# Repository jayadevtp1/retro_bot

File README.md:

# Desktop Bot

Desktop Bot is a mini AI companion robot built to sit right on my desk and bring a bit of personality to my workspace. Inspired by the M5Stack Chan AI bot and the nostalgic charm of vintage CRT monitors, I wanted to create a compact, expressive desk buddy that can react, chat
and emotions on a crisp 2-inch LCD screen.

# Features

• Animated Facial Expressions: Displays expressive eyes and emotions on a crisp 2-inch LCD screen.

• Built-in Voice Interaction: Listens and talks back naturally using an onboard digital mic and speaker amplifier.

• Desk Utilities: Doubles as a handy desk gadget with a digital clock and ambient temperature display.

• Capacitive Touch Interaction: Responds to gentle taps and head pats with playful expressions and reactions.
# Schematic & PCB

# Final Assembly

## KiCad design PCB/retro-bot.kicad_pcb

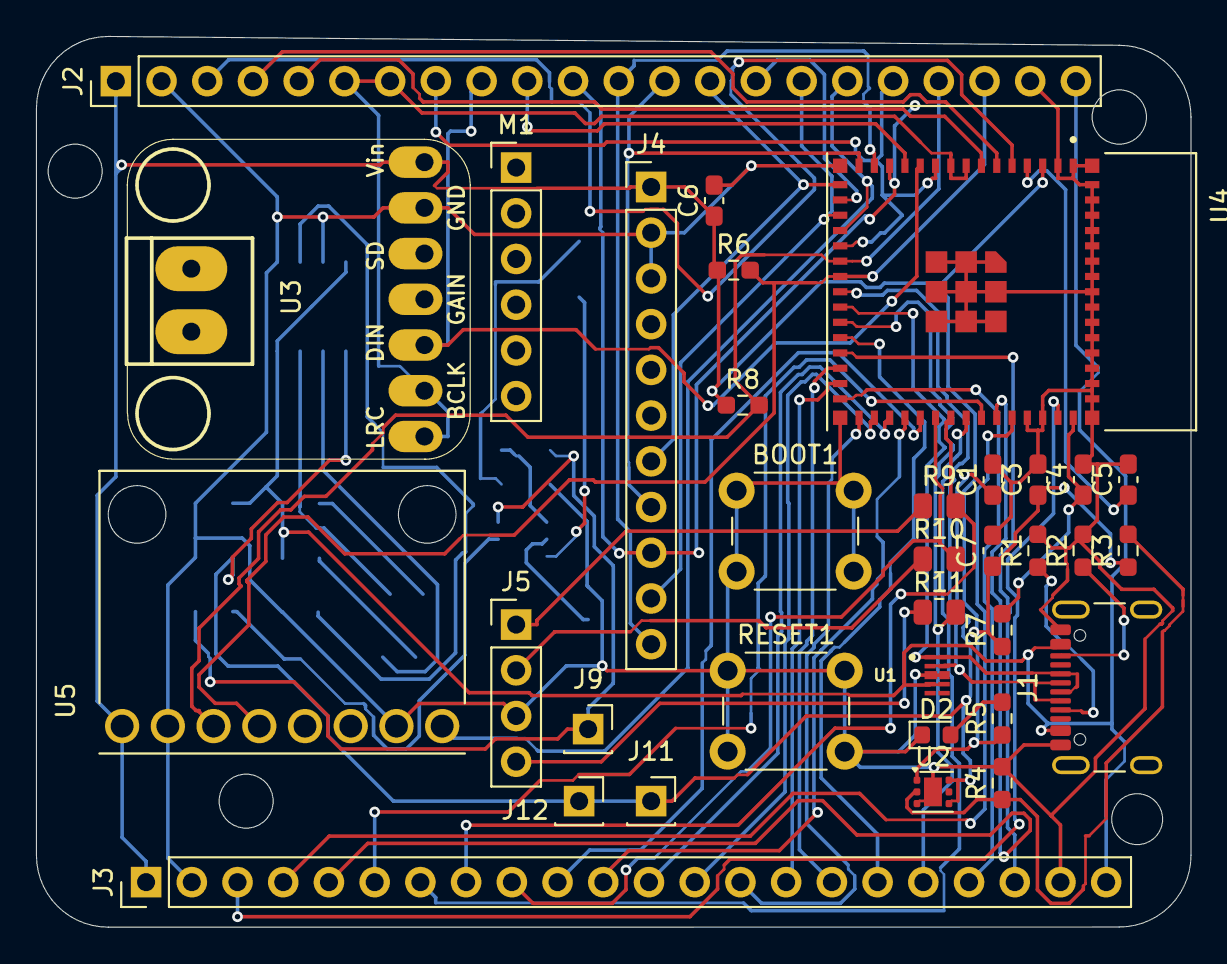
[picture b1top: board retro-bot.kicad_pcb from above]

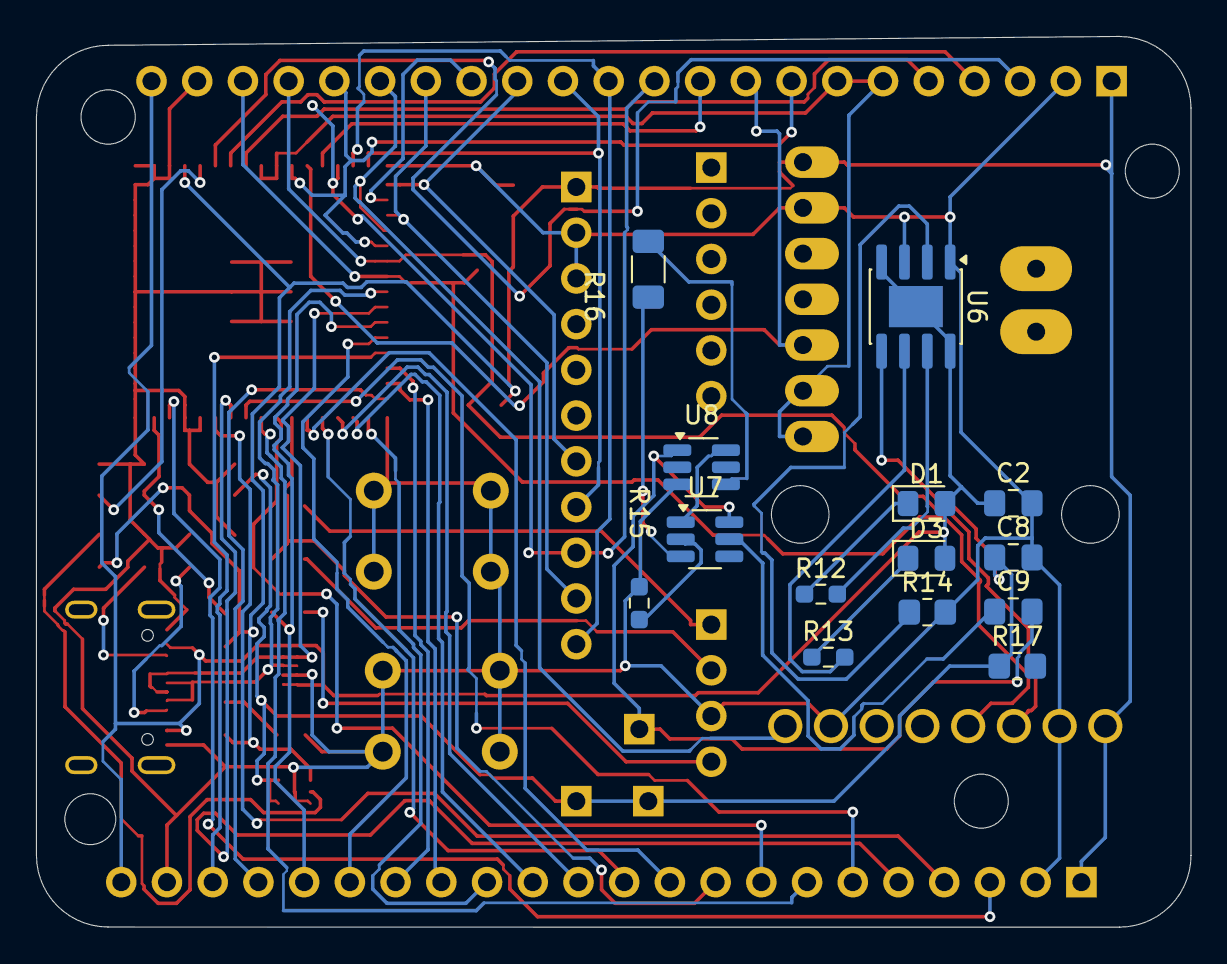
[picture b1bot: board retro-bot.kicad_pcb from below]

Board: 2 copper layers, 64.1 x 49.5 mm, 48 parts (14 on the bottom side), 60 nets.

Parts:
BOOT1: SW_MEC_5E; SW_PUSH_6mm
C1, C3, C7: 10uF; C_0603_1608Metric_Pad1.08x0.95mm_HandSolder
C2, C9: 0.1uF; C_0805_2012Metric_Pad1.18x1.45mm_HandSolder
C4, C5, C6: 0.1uF; C_0603_1608Metric_Pad1.08x0.95mm_HandSolder
C8: 10uF; C_0805_2012Metric_Pad1.18x1.45mm_HandSolder
D1: RED; LED_0805_2012Metric_Pad1.15x1.40mm_HandSolder
D2: LED; LED_0603_1608Metric
D3: GREEN; LED_0805_2012Metric_Pad1.15x1.40mm_HandSolder
J1: USB_C_Receptacle_USB2.0_16P; USB_C_Receptacle_GCT_USB4105-xx-A_16P_TopMnt_Horizontal
J2, J3: Conn_01x22_Pin; PinHeader_1x22_P2.54mm_Vertical
J4: Conn_01x11_Pin; PinHeader_1x11_P2.54mm_Vertical
J5: Conn_01x04_Pin; PinHeader_1x04_P2.54mm_Vertical
J9, J11, J12: Conn_01x01_Female; PinSocket_1x01_P2.54mm_Vertical
M1: PinHeader_1x06_P2.54mm_Vertical
R1, R2: 5.1k; R_0603_1608Metric_Pad0.98x0.95mm_HandSolder
R3: 1M; R_0603_1608Metric_Pad0.98x0.95mm_HandSolder
R4: 200k; R_0603_1608Metric_Pad0.98x0.95mm_HandSolder
R5: 680; R_0603_1608Metric_Pad0.98x0.95mm_HandSolder
R6, R7, R8: 10k; R_0603_1608Metric_Pad0.98x0.95mm_HandSolder
R9, R10, R11: 120ohm; R_0805_2012Metric
R12, R13, R15: 1k; R_0603_1608Metric_Pad0.98x0.95mm_HandSolder
R14: 10k; R_0805_2012Metric_Pad1.20x1.40mm_HandSolder
R16: 0R; R_1206_3216Metric_Pad1.30x1.75mm_HandSolder
R17: 100; R_0805_2012Metric_Pad1.20x1.40mm_HandSolder
RESET1: SW_MEC_5E; SW_PUSH_6mm
U1: D3V3XA4B10LP; DIO_DT1240-04LP-7
U2: TLV75801PDRV; WSON-6-1EP_2x2mm_P0.65mm_EP1x1.6mm
U3: adafruit-MAX98357
U4: ESP32-S3-MINI-1-N8; XCVR_ESP32-S3-MINI-1-N8
U5: OC09600; MODULE_OC09600
U6: TP4056; SOIC-8-1EP_3.9x4.9mm_P1.27mm_EP2.29x3mm
U7: DW01; SOT-23-6_Handsoldering
U8: FS8205A; SOT-23-6_Handsoldering

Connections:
/3V3: C3.1, C6.1, C7.1, J2.1, J3.1, J4.1, R3.1, R5.1, R6.1, R7.1, R8.1, U2.1 (OUT), U3.1 (Vin), U4.3 (3V3), U5.VCC
/5VUSB: C2.1, D1.2 (A), D3.2 (A), J1.A4 (VBUS), J1.A9 (VBUS), J1.B4 (VBUS), J1.B9 (VBUS), J2.22, J3.22, U1.4, U1.7 (NC), U6.4 (VCC), U6.8 (CE), U6.9 (PP)
/CLK: J2.14, J4.7, U4.16 (IO12)
/CS: J2.12, J4.11, U4.14 (IO10)
/ESP32_EN: C4.1, R7.2, U4.45 (EN)
/G1: U7.1 (OD), U8.6 (G1)
/G2: R16.2, U8.4 (G2)
/GPIO0: C5.1, U4.4 (IO0)
/GPIO1: J2.3, U4.5 (IO1)
/GPIO2: J2.4, U4.6 (IO2)
/GPIO3: J2.5, U4.7 (IO3)
/GPIO4: J2.6, J2.7, U3.6 (BCLK), U3.7 (LRC), U4.8 (IO4), U4.9 (IO5)
/GPIO8: J2.10, U4.12 (IO8)
/GPIO9: J2.11, J4.9, U4.13 (IO9)
/GPIO11: J2.13, J4.8, U4.15 (IO11)
/GPIO13: J2.15, U4.17 (IO13)
/GPIO14: J2.16, J4.10, U4.18 (IO14)
/GPIO15: J2.17, U4.19 (IO15), U5.INT
/GPIO16: J2.8, J2.18, U4.10 (IO6), U4.20 (IO16)
/GPIO17: J2.9, U3.5 (DIN), U4.11 (IO7)
/GPIO21: J3.18, R11.2, U4.25 (IO21)
/GPIO26: J3.17, U4.26 (IO26)
/GPIO33: J3.16, U4.28 (IO33)
/GPIO34: J3.15, U4.29 (IO34)
/GPIO35: J3.14, U4.31 (IO35)
/GPIO36: J3.13, U4.32 (IO36)
/GPIO37: J3.12, U4.33 (IO37)
/GPIO38: J3.11, U4.34 (IO38)
/GPIO39: J3.10, U4.35 (IO39)
/GPIO40: J3.9, R10.2, U4.36 (IO40)
/GPIO41: J3.8, R9.2, U4.37 (IO41)
/GPIO42: J3.7, U4.38 (IO42)
/GPIO45: J3.4, U4.41 (IO45)
/GPIO46: J3.3, U4.44 (IO46)
/GPIO47: J3.20, U4.27 (IO47)
/GPIO48: J3.19, U4.30 (IO48)
/I2C_SCL: J2.19, R8.2, U4.21 (IO17), U5.SCL
/I2C_SDA: J2.20, R6.2, U4.22 (IO18), U5.SDA
/OC: R16.1, U7.3 (OC)
/RXD: J3.5, U4.40 (RXD0)
/TXD: J3.6, U4.39 (TXD0)
/USB+: J1.A6 (D+), J1.B6 (D+), U1.1, U1.10 (NC), U4.24 (IO20)
/USB-: J1.A7 (D-), J1.B7 (D-), U1.2, U1.9 (NC), U4.23 (IO19)
BAT+: C1.1, C8.1, J11.1 (Pin_1_1), J12.1 (Pin_1_1), R17.1, U2.4 (EN), U2.6 (IN), U6.5 (BAT)
BAT-: C9.2, J9.1 (Pin_1_1), U7.6 (GND), U8.1 (S1)
Earth: BOOT1.1, BOOT1.2, C1.2, C2.2, C3.2, C4.2, C5.2, C6.2, C7.2, C8.2, D2.1 (K), J1.A1 (GND), J1.A12 (GND), J1.B1 (GND), J1.B12 (GND), J2.2, J2.21, J3.2, J3.21, J4.2, J4.3, J5.3, R1.2, R2.2, R4.2, R14.2, R15.1, RESET1.1, RESET1.2, U1.3 (VSS), U1.8 (VSS), U2.3 (GND), U2.7 (GND), U3.2 (GND), U4.1 (GND), U4.2 (GND), U4.42 (GND), U4.43 (GND), U4.46 (GND), U4.47 (GND), U4.48 (GND), U4.49 (GND), U4.50 (GND), U4.51 (GND), U4.52 (GND), U4.53 (GND), U4.54 (GND), U4.55 (GND), U4.56 (GND), U4.57 (GND), U4.58 (GND), U4.59 (GND), U4.60 (GND), U4.61 (GND), U4.61_1 (GND), U4.61_2 (GND), U4.61_3 (GND), U4.61_4 (GND), U4.61_5 (GND), U4.61_6 (GND), U4.61_7 (GND), U4.61_8 (GND), U4.62 (GND), U4.63 (GND), U4.64 (GND), U4.65 (GND), U5.AD0, U5.GND, U6.1 (TEMP), U6.3 (GND), U8.3 (S2)
unnamed: D1.1 (K), R12.1
unnamed: D2.2 (A), R5.2
unnamed: D3.1 (K), R13.1
unnamed: J1.A5 (CC1), R1.1
unnamed: J1.B5 (CC2), R2.1
unnamed: J5.1, R9.1
unnamed: J5.2, R10.1
unnamed: J5.4, R11.1
unnamed: R3.2, R4.1, U2.2 (FB)
unnamed: R14.1, U6.2 (PROG)
unnamed: R12.2, U6.7 (~CHRG)
unnamed: R13.2, U6.6 (~STDBY)
unnamed: R15.2, U7.2 (CS)
unnamed: C9.1, U7.5 (VCC)

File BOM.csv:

| Id | Designator | Component Name | Footprint | Quantity | Unit Cost (INR) | Total Cost (INR) | Supplier |
| :- | :--- | :--- | :--- | :---: | :---: | :---: | :--- |
| 1 | BOOT1, RESET1 | Tactile Push Button Switch | `SW_PUSH_6mm` | 2 | 1.90 | 3.80 | [Robu.in](https://robu.in) |
| 2 | C1, C3, C7 | 10uF MLCC Capacitor | `C_0603_1608Metric` | 3 | 2.00 | 6.00 | [Robu.in](https://robu.in) |
| 3 | C2, C9 | 0.1uF MLCC Capacitor | `C_0805_2012Metric` | 2 | 1.50 | 3.00 | [Robu.in](https://robu.in) |
| 4 | C4, C5, C6 | 0.1uF MLCC Capacitor | `C_0603_1608Metric` | 3 | 1.50 | 4.50 | [Robu.in](https://robu.in) |
| 5 | C8 | 10uF MLCC Capacitor | `C_0805_2012Metric` | 1 | 2.50 | 2.50 | [Robu.in](https://robu.in) |
| 6 | D1 | RED SMD LED | `LED_0805_2012Metric` | 1 | 0.97 | 0.97 | [Robu.in](https://robu.in) |
| 7 | D2 | Indicator SMD LED | `LED_0603_1608Metric` | 1 | 1.00 | 1.00 | [Robu.in](https://robu.in) |
| 8 | D3 | GREEN SMD LED | `LED_0805_2012Metric` | 1 | 0.54 | 0.54 | [Robu.in](https://robu.in) |
| 9 | J1 | GCT USB4105-GF-A USB-C Receptacle | `USB_C_Receptacle_GCT_USB4105-xx-A_16P` | 1 | 83.57 | 83.57 | [Element14](https://element14.com) |
| 10 | J2, J3 | Conn_01x22_Pin Male Header | `PinHeader_1x22_P2.54mm_Vertical` | 2 | 10.00 | 20.00 | [Robu.in](https://robu.in) |
| 11 | J4 | Conn_01x11_Pin Male Header | `PinHeader_1x11_P2.54mm_Vertical` | 1 | 6.00 | 6.00 | [Robu.in](https://robu.in) |
| 12 | J9, J11, J12 | Conn_01x01_Female Socket | `PinSocket_1x01_P2.54mm_Vertical` | 3 | 5.00 | 15.00 | [Robu.in](https://robu.in) |
| 13 | M1 | Conn_01x06_Pin Male Header | `PinHeader_1x06_P2.54mm_Vertical` | 1 | 5.00 | 5.00 | [Robu.in](https://robu.in) |
| 14 | R1, R2 | 5.1k Ohm SMD Resistor | `R_0603_1608Metric` | 2 | 0.40 | 0.80 | [Robu.in](https://robu.in) |
| 15 | R3 | 1M Ohm SMD Resistor | `R_0603_1608Metric` | 1 | 0.40 | 0.40 | [Robu.in](https://robu.in) |
| 16 | R4 | 200k Ohm SMD Resistor | `R_0603_1608Metric` | 1 | 0.40 | 0.40 | [Robu.in](https://robu.in) |
| 17 | R5 | 680 Ohm SMD Resistor | `R_0603_1608Metric` | 1 | 0.40 | 0.40 | [Robu.in](https://robu.in) |
| 18 | R6, R7, R8 | 10k Ohm SMD Resistor | `R_0603_1608Metric` | 3 | 0.40 | 1.20 | [Robu.in](https://robu.in) |
| 19 | R9, R10, R11 | 120 Ohm SMD Resistor | `R_0805_2012Metric` | 3 | 0.40 | 1.20 | [Robu.in](https://robu.in) |
| 20 | R12, R13, R15 | 1k Ohm SMD Resistor | `R_0603_1608Metric` | 3 | 0.40 | 1.20 | [Robu.in](https://robu.in) |
| 21 | R14 | 10k Ohm SMD Resistor | `R_0805_2012Metric` | 1 | 0.51 | 0.51 | [Robu.in](https://robu.in) |
| 22 | R16 | 0R Jumper SMD Resistor | `R_1206_3216Metric` | 1 | 0.39 | 0.39 | [Robu.in](https://robu.in) |
| 23 | R17 | 100 Ohm SMD Resistor | `R_0805_2012Metric` | 1 | 0.40 | 0.40 | [Robu.in](https://robu.in) |
| 24 | U1 | D3V3XA4B10LP-7 ESD Protection | `DIO_DT1240-04LP-7` | 1 | 43.95 | 43.95 | [Mouser.in](https://mouser.in) |
| 25 | U2 | TLV75801PDRVR LDO Regulator | `WSON-6-1EP_2x2mm` | 1 | 33.44 | 33.44 | [Mouser.in](https://mouser.in) |
| 26 | U3 | MAX98357 I2S Amplifier Module | `adafruit-MAX98357` | 1 | 179.00 | 179.00 | [Robu.in](https://robu.in) |
| 27 | U4 | ESP32-S3-MINI-1-N8 Module | `XCVR_ESP32-S3-MINI-1-N8` | 1 | 399.00 | 399.00 | [Robu.in](https://robu.in) |
| 28 | U5 | MPU-6050 IMU Module (OC09600) | `MODULE_OC09600` | 1 | 199.00 | 199.00 | [Robu.in](https://robu.in) |
| 29 | U6 | TP4056 Li-Ion Charger IC | `SOIC-8-1EP` | 1 | 13.00 | 13.00 | [Robu.in](https://robu.in) |
| 30 | U7 | DW01 Battery Protection IC | `SOT-23-6` | 1 | 8.00 | 8.00 | [Robu.in](https://robu.in) |
| 31 | U8 | FS8205A Dual MOSFET | `SOT-23-6` | 1 | 9.00 | 9.00 | [Robu.in](https://robu.in) |
| | | **Total** | | **47** | | **1043.17** | |
